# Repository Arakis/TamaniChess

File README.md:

TamaniChess
-----------

TamaniChess is a open source chess computer. This project contains:
* The construction plan of the chess computer
  * the wodden case
  * the electrical circuits
  * needed parts
* The software, written in C#. It controls the chess board, the display and the chess engine
* The "Stockfish" chess engine: http://stockfishchess.org/

Common Questions
----------------

Q. Is TamaniChess Open Source?  
A. TamaniChess's License is a modified version of the standard BSD license. The primary modification is that we do not allow commercial distribution or use of TamaniChess, in order to limit some of the obvious abuses of the code and construction plans. Because of this modification, TamaniChess's license does not fall under the definition of an Open Source (uppercase) license.
Confusingly, TamaniChess is often referred to as open source (lowercase), as its development shares much in common with other open source projects. However, in spite of its freely available source code, TamaniChess may not be used in a commercial setting, as specified by its license.

Q. Can I include TamaniChess with my product?  
A. No. TamaniChess is not licensed for commercial use. Using TamaniChess as a "freebie" or including it at "no cost" with your product still constitutes commerical usage and is forbidden by the license.

Q. Can I sell my product with the TamaniChess logo on it?  
A. No. Putting the logo on your product makes it appear that the product is something officially endorsed by Sebastian Loncar, and constitutes trademark infringement.

Q. Can I use the TamaniChess logo to advertise my product?  
A. No. Using the logo in your advertising makes it appear that the product is something officially endorsed by Sebastian Loncar, and constitutes trademark infringement.

Q. Can I use the term "TamaniChess" in the name of my software?  
A. Generally, no, especially if it is something that is sold. However, if you are producing a free TamaniChess-related piece of software, it is common that permission is granted. Send a query to double- check first, please.

Q. Can I put an arcade cabinet running TamaniChess in a public location?  
A. No. This this a commercial use of TamaniChess and is prohibited by the license. Even if you don't charge money, putting a machine in a public location is "operating" an arcade machine and falls under commercial rules in most locations.

Q. Can my non-profit use TamaniChess or an arcade cabinet running TamaniChess to help raise money?  
A. No, sorry. Even for the most worthwhile cause, this still is a commercial use of TamaniChess and is prohibited by the license.

Q. How do I obtain a license to the TamaniChess source code?  
A. You can't. See the Copyright section above.

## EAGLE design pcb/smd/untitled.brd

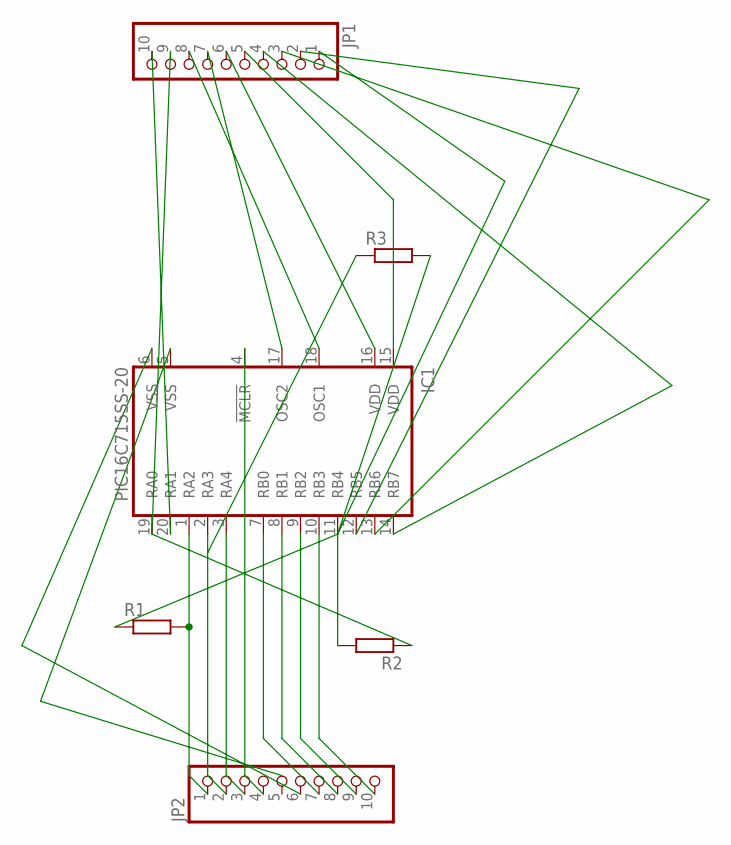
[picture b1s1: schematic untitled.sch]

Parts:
IC1: PIC16C715SS-20; SSOP20
JP1, JP2: PINHD-1X10; 1X10
R1: R-EU_0207/10; 0207/10
R2, R3: R-EU_0204/2V; 0204V

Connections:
unnamed: IC1.1 (RA2), JP2.1, R1.2
unnamed: IC1.2 (RA3), JP2.2, R3.1
unnamed: IC1.3 (RA4), JP2.3
unnamed: IC1.4 (!MCLR), JP2.4
unnamed: IC1.6 (VSS), JP2.6
unnamed: IC1.7 (RB0), JP2.7
unnamed: IC1.8 (RB1), JP2.8
unnamed: IC1.9 (RB2), JP2.9
unnamed: IC1.10 (RB3), JP2.10
unnamed: IC1.11 (RB4), JP1.1, R1.1, R2.2, R3.2
unnamed: IC1.12 (RB5), JP1.2
unnamed: IC1.13 (RB6), JP1.3
unnamed: IC1.14 (RB7), JP1.4
unnamed: IC1.15 (VDD), JP1.5
unnamed: IC1.16 (VDD), JP1.6
unnamed: IC1.17 (OSC2), JP1.7
unnamed: IC1.18 (OSC1), JP1.8
unnamed: IC1.19 (RA0), JP1.9, R2.1
unnamed: IC1.20 (RA1), JP1.10

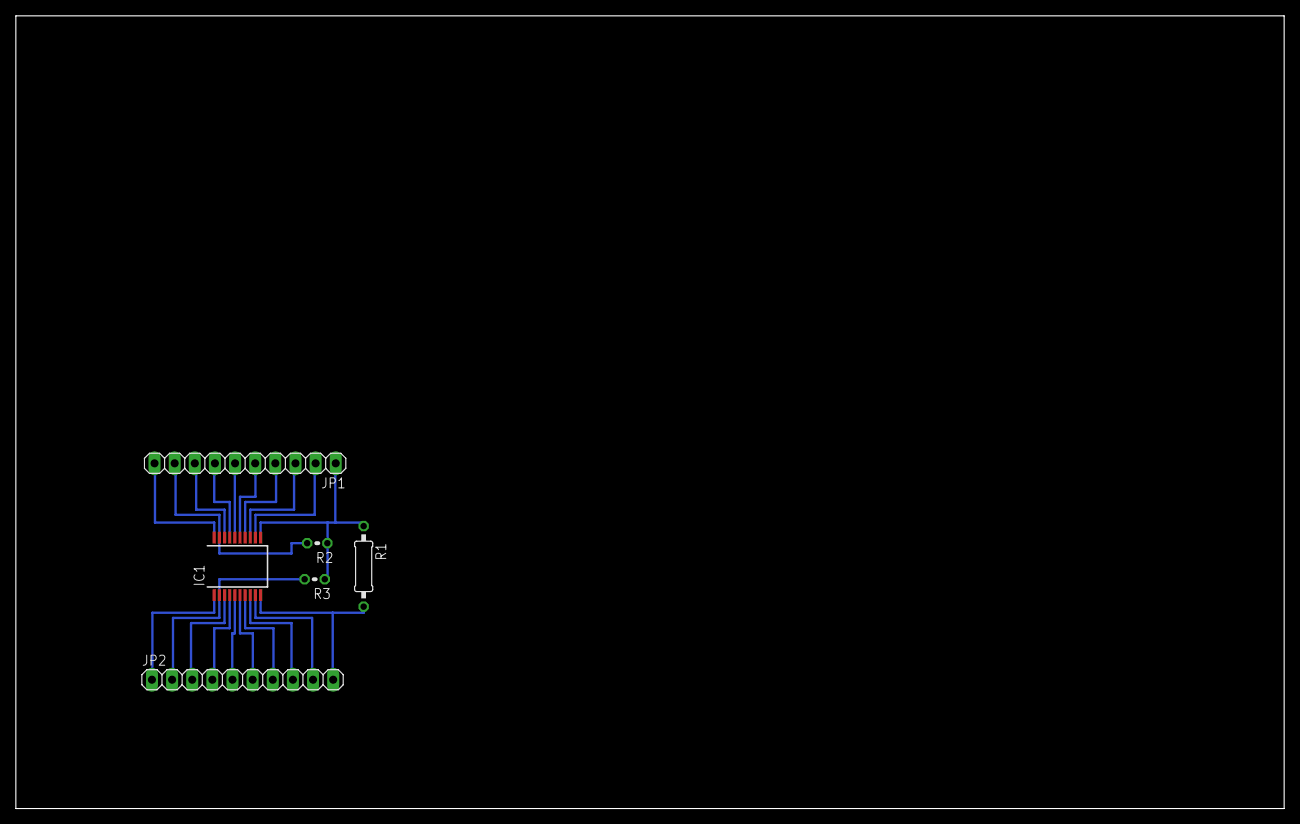
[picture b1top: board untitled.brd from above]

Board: 2 copper layers, 160.0 x 100.0 mm, 6 parts (0 on the bottom side), 19 nets.

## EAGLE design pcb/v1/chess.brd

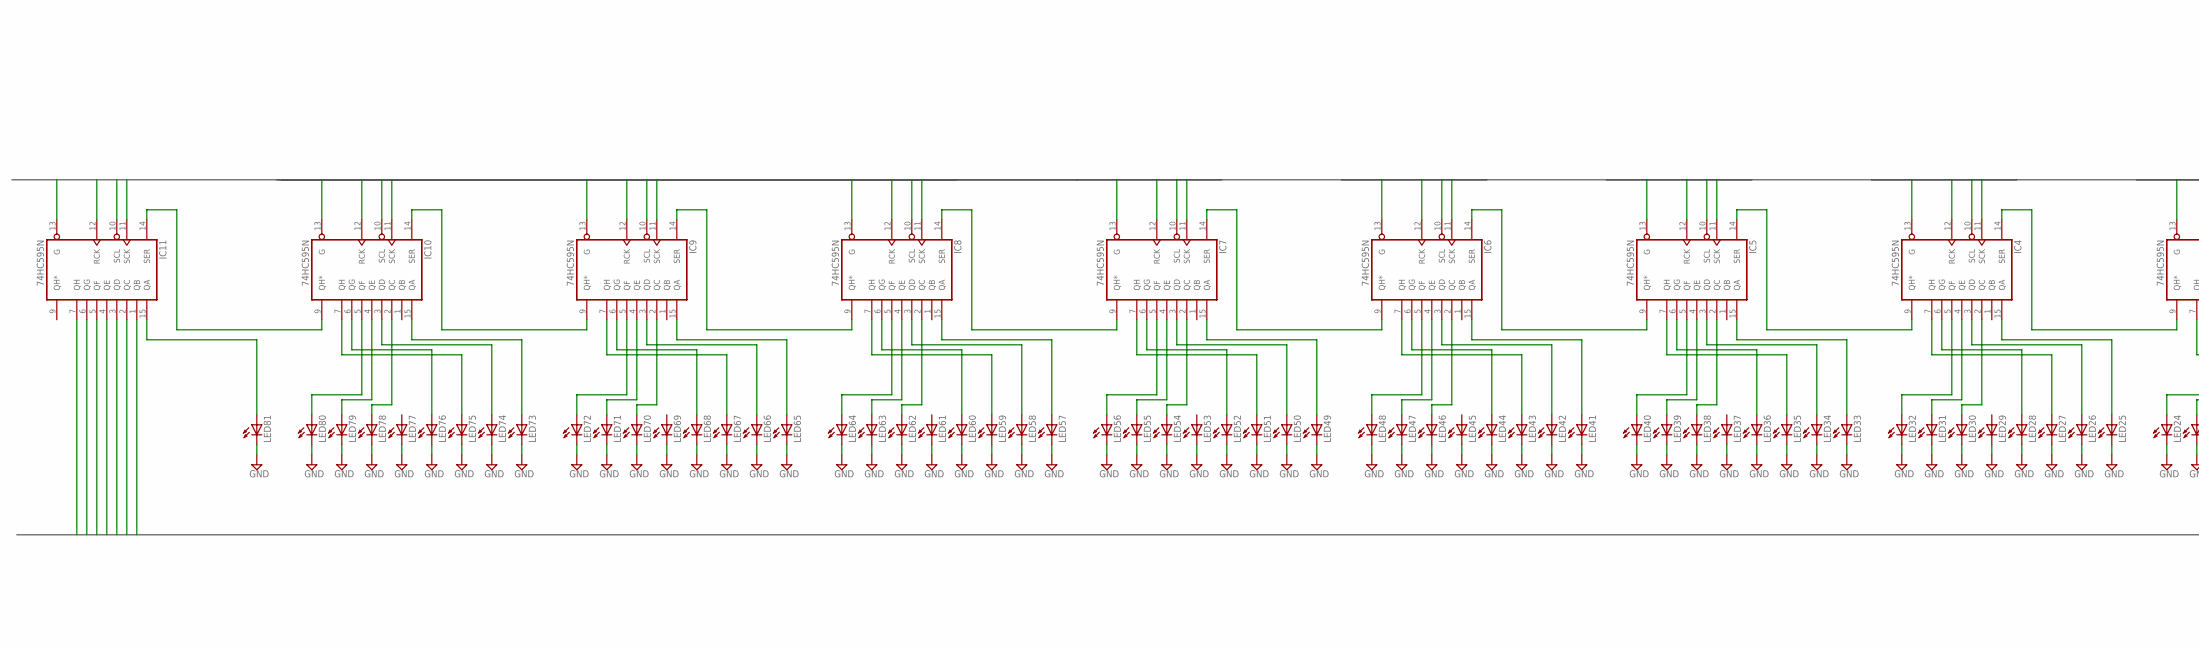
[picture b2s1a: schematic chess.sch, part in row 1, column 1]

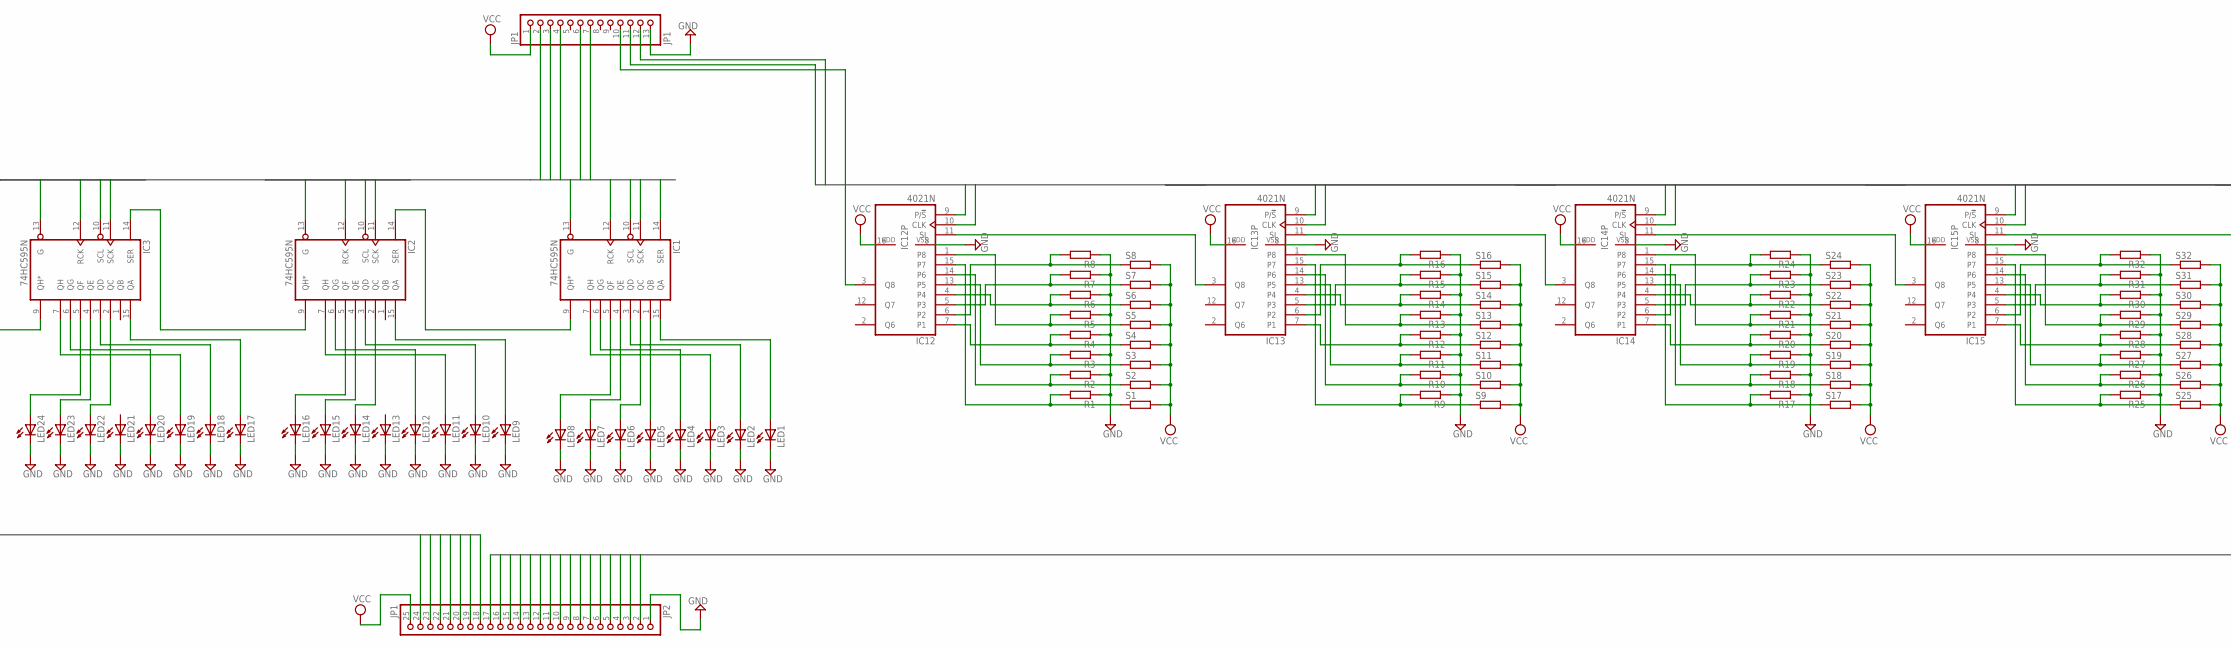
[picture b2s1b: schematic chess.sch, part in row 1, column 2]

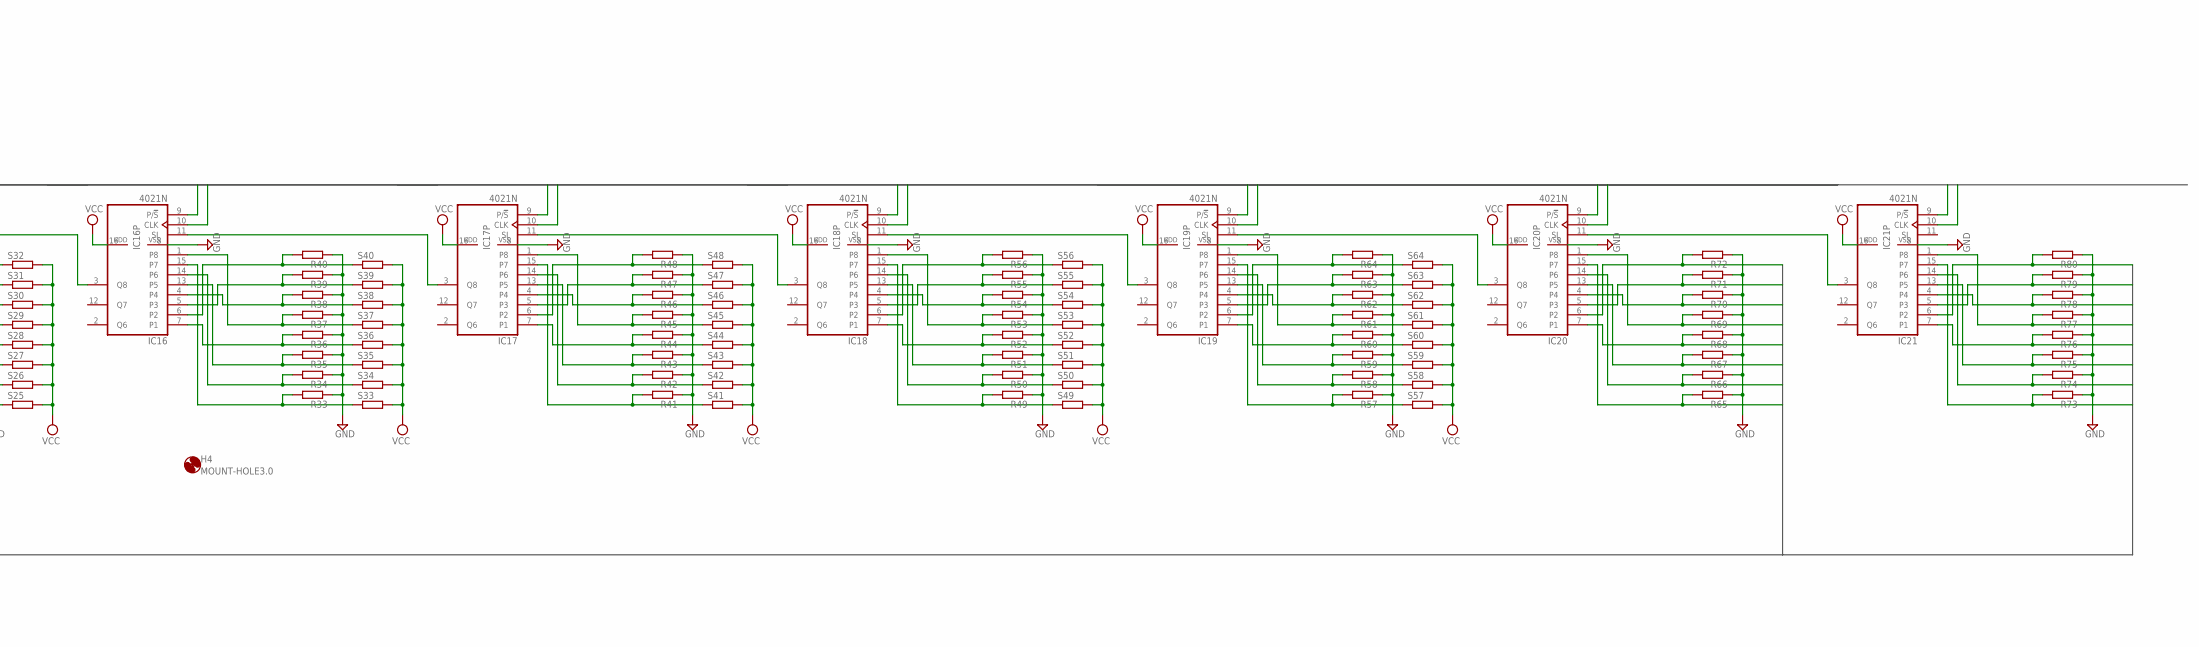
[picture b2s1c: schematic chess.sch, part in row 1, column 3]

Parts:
H4: MOUNT-HOLE3.0; 3,0
IC1, IC2, IC3, IC4, IC5, IC6, IC7, IC8, IC9, IC10, IC11: 74HC595N; DIL16
IC12, IC13, IC14, IC15, IC16, IC17, IC18, IC19, IC20, IC21: 4021N; DIL16
JP1: JP1; 1X13
JP2: JP1; 1X25
LED1, LED2, LED3, LED4, LED5, LED6, LED7, LED8, LED9, LED10, LED11, LED12, LED13, LED14, LED15, LED16, LED17, LED18, LED19, LED20, LED21, LED22, LED23, LED24, LED25, LED26, LED27, LED28, LED29, LED30, LED31, LED32, LED33, LED34, LED35, LED36, LED37, LED38, LED39, LED40, LED41, LED42, LED43, LED44, LED45, LED46, LED47, LED48, LED49, LED50, LED51, LED52, LED53, LED54, LED55, LED56, LED57, LED58, LED59, LED60, LED61, LED62, LED63, LED64, LED65, LED66, LED67, LED68, LED69, LED70, LED71, LED72, LED73, LED74, LED75, LED76, LED77, LED78, LED79, LED80, LED81: LED5MM
R1, R2, R3, R4, R5, R6, R7, R8, R9, R10, R11, R12, R13, R14, R15, R16, R17, R18, R19, R20, R21, R22, R23, R24, R25, R26, R27, R28, R29, R30, R31, R32, R33, R34, R35, R36, R37, R38, R39, R40, R41, R42, R43, R44, R45, R46, R47, R48, R49, R50, R51, R52, R53, R54, R55, R56, R57, R58, R59, R60, R61, R62, R63, R64, R65, R66, R67, R68, R69, R70, R71, R72, R73, R74, R75, R76, R77, R78, R79, R80: R-EU_0207/15; 0207/15
S1, S2, S3, S4, S5, S6, S7, S8, S9, S10, S11, S12, S13, S14, S15, S16, S17, S18, S19, S20, S21, S22, S23, S24, S25, S26, S27, S28, S29, S30, S31, S32, S33, S34, S35, S36, S37, S38, S39, S40, S41, S42, S43, S44, S45, S46, S47, S48, S49, S50, S51, S52, S53, S54, S55, S56, S57, S58, S59, S60, S61, S62, S63, S64: R-EU_0617/22; 0617/22

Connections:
CLK: IC12.10 (CLK), IC13.10 (CLK), IC14.10 (CLK), IC15.10 (CLK), IC16.10 (CLK), IC17.10 (CLK), IC18.10 (CLK), IC19.10 (CLK), IC20.10 (CLK), IC21.10 (CLK), JP1.11
G: IC1.13 (G), IC2.13 (G), IC3.13 (G), IC4.13 (G), IC5.13 (G), IC6.13 (G), IC7.13 (G), IC8.13 (G), IC9.13 (G), IC10.13 (G), IC11.13 (G), JP1.3
GND: IC1.8 (GND), IC2.8 (GND), IC3.8 (GND), IC4.8 (GND), IC5.8 (GND), IC6.8 (GND), IC7.8 (GND), IC8.8 (GND), IC9.8 (GND), IC10.8 (GND), IC11.8 (GND), IC12.8 (VSS), IC13.8 (VSS), IC14.8 (VSS), IC15.8 (VSS), IC16.8 (VSS), IC17.8 (VSS), IC18.8 (VSS), IC19.8 (VSS), IC20.8 (VSS), IC21.8 (VSS), JP1.13, JP2.1, LED1.K (C), LED2.K (C), LED3.K (C), LED4.K (C), LED5.K (C), LED6.K (C), LED7.K (C), LED8.K (C), LED9.K (C), LED10.K (C), LED11.K (C), LED12.K (C), LED13.K (C), LED14.K (C), LED15.K (C), LED16.K (C), LED17.K (C), LED18.K (C), LED19.K (C), LED20.K (C), LED21.K (C), LED22.K (C), LED23.K (C), LED24.K (C), LED25.K (C), LED26.K (C), LED27.K (C), LED28.K (C), LED29.K (C), LED30.K (C), LED31.K (C), LED32.K (C), LED33.K (C), LED34.K (C), LED35.K (C), LED36.K (C), LED37.K (C), LED38.K (C), LED39.K (C), LED40.K (C), LED41.K (C), LED42.K (C), LED43.K (C), LED44.K (C), LED45.K (C), LED46.K (C), LED47.K (C), LED48.K (C), LED49.K (C), LED50.K (C), LED51.K (C), LED52.K (C), LED53.K (C), LED54.K (C), LED55.K (C), LED56.K (C), LED57.K (C), LED58.K (C), LED59.K (C), LED60.K (C), LED61.K (C), LED62.K (C), LED63.K (C), LED64.K (C), LED65.K (C), LED66.K (C), LED67.K (C), LED68.K (C), LED69.K (C), LED70.K (C), LED71.K (C), LED72.K (C), LED73.K (C), LED74.K (C), LED75.K (C), LED76.K (C), LED77.K (C), LED78.K (C), LED79.K (C), LED80.K (C), LED81.K (C), R1.1, R2.1, R3.1, R4.1, R5.1, R6.1, R7.1, R8.1, R9.1, R10.1, R11.1, R12.1, R13.1, R14.1, R15.1, R16.1, R17.1, R18.1, R19.1, R20.1, R21.1, R22.1, R23.1, R24.1, R25.1, R26.1, R27.1, R28.1, R29.1, R30.1, R31.1, R32.1, R33.1, R34.1, R35.1, R36.1, R37.1, R38.1, R39.1, R40.1, R41.1, R42.1, R43.1, R44.1, R45.1, R46.1, R47.1, R48.1, R49.1, R50.1, R51.1, R52.1, R53.1, R54.1, R55.1, R56.1, R57.1, R58.1, R59.1, R60.1, R61.1, R62.1, R63.1, R64.1, R65.1, R66.1, R67.1, R68.1, R69.1, R70.1, R71.1, R72.1, R73.1, R74.1, R75.1, R76.1, R77.1, R78.1, R79.1, R80.1
unnamed: IC1.9 (QH*), IC2.14 (SER)
unnamed: IC2.15 (QA), LED9.A
unnamed: IC1.15 (QA), LED1.A
unnamed: IC1.1 (QB), LED5.A
unnamed: IC1.2 (QC), LED6.A
unnamed: IC1.3 (QD), LED2.A
unnamed: IC1.4 (QE), LED7.A
unnamed: IC1.5 (QF), LED8.A
unnamed: IC1.6 (QG), LED4.A
unnamed: IC1.7 (QH), LED3.A
unnamed: IC2.2 (QC), LED14.A
unnamed: IC2.3 (QD), LED10.A
unnamed: IC2.4 (QE), LED15.A
unnamed: IC2.5 (QF), LED16.A
unnamed: IC2.6 (QG), LED12.A
unnamed: IC2.7 (QH), LED11.A
unnamed: IC3.15 (QA), LED17.A
unnamed: IC3.2 (QC), LED22.A
unnamed: IC3.3 (QD), LED18.A
unnamed: IC3.4 (QE), LED23.A
unnamed: IC3.5 (QF), LED24.A
unnamed: IC3.6 (QG), LED20.A
unnamed: IC3.7 (QH), LED19.A
unnamed: IC4.15 (QA), LED25.A
unnamed: IC4.2 (QC), LED30.A
unnamed: IC4.3 (QD), LED26.A
unnamed: IC4.4 (QE), LED31.A
unnamed: IC2.9 (QH*), IC3.14 (SER)
unnamed: IC4.5 (QF), LED32.A
unnamed: IC4.6 (QG), LED28.A
unnamed: IC4.7 (QH), LED27.A
unnamed: IC5.15 (QA), LED33.A
unnamed: IC5.2 (QC), LED38.A
unnamed: IC5.3 (QD), LED34.A
unnamed: IC5.4 (QE), LED39.A
unnamed: IC5.5 (QF), LED40.A
unnamed: IC5.6 (QG), LED36.A
unnamed: IC3.9 (QH*), IC4.14 (SER)
unnamed: IC5.7 (QH), LED35.A
unnamed: IC6.15 (QA), LED41.A
unnamed: IC6.2 (QC), LED46.A
unnamed: IC6.3 (QD), LED42.A
unnamed: IC6.4 (QE), LED47.A
unnamed: IC6.5 (QF), LED48.A
unnamed: IC6.6 (QG), LED44.A
unnamed: IC6.7 (QH), LED43.A
unnamed: IC7.15 (QA), LED49.A
unnamed: IC4.9 (QH*), IC5.14 (SER)
unnamed: IC7.2 (QC), LED54.A
unnamed: IC7.3 (QD), LED50.A
unnamed: IC7.4 (QE), LED55.A
unnamed: IC7.5 (QF), LED56.A
unnamed: IC7.6 (QG), LED52.A
unnamed: IC7.7 (QH), LED51.A
unnamed: IC8.15 (QA), LED57.A
unnamed: IC8.2 (QC), LED62.A
unnamed: IC8.3 (QD), LED58.A
unnamed: IC5.9 (QH*), IC6.14 (SER)
unnamed: IC8.4 (QE), LED63.A
unnamed: IC8.5 (QF), LED64.A
unnamed: IC8.6 (QG), LED60.A
unnamed: IC8.7 (QH), LED59.A
unnamed: IC9.15 (QA), LED65.A
unnamed: IC9.2 (QC), LED70.A
unnamed: IC9.3 (QD), LED66.A
unnamed: IC9.4 (QE), LED71.A
unnamed: IC9.5 (QF), LED72.A
unnamed: IC6.9 (QH*), IC7.14 (SER)
unnamed: IC9.6 (QG), LED68.A
unnamed: IC9.7 (QH), LED67.A
unnamed: IC10.15 (QA), LED73.A
unnamed: IC10.2 (QC), LED78.A
unnamed: IC10.3 (QD), LED74.A
unnamed: IC10.4 (QE), LED79.A
unnamed: IC10.5 (QF), LED80.A
unnamed: IC10.6 (QG), LED76.A
unnamed: IC10.7 (QH), LED75.A
unnamed: IC7.9 (QH*), IC8.14 (SER)
unnamed: IC12.1 (P8), R5.2, S5.1
unnamed: IC8.9 (QH*), IC9.14 (SER)
unnamed: IC13.6 (P2), R16.2, S16.1
unnamed: IC13.13 (P5), R11.2, S11.1
unnamed: IC13.7 (P1), R12.2, S12.1
unnamed: IC13.4, R14.2, S14.1
unnamed: IC13.5 (P3), R15.2, S15.1
unnamed: IC13.14 (P6), R10.2, S10.1
unnamed: IC13.15 (P7), R9.2, S9.1
unnamed: IC13.1 (P8), R13.2, S13.1
unnamed: IC9.9 (QH*), IC10.14 (SER)
unnamed: IC12.3 (Q8), JP1.10
unnamed: IC12.6 (P2), R8.2, S8.1
unnamed: IC14.6 (P2), R24.2, S24.1
unnamed: IC12.4, R6.2, S6.1
unnamed: IC12.13 (P5), R3.2, S3.1
unnamed: IC12.7 (P1), R4.2, S4.1
unnamed: IC12.5 (P3), R7.2, S7.1
unnamed: IC11.15 (QA), LED81.A
unnamed: IC10.9 (QH*), IC11.14 (SER)
unnamed: IC12.14 (P6), R2.2, S2.1
unnamed: IC12.15 (P7), R1.2, S1.1
unnamed: IC14.13 (P5), R19.2, S19.1
unnamed: IC14.7 (P1), R20.2, S20.1
unnamed: IC14.4, R22.2, S22.1
unnamed: IC14.5 (P3), R23.2, S23.1
unnamed: IC14.14 (P6), R18.2, S18.1
unnamed: IC14.15 (P7), R17.2, S17.1
unnamed: IC14.1 (P8), R21.2, S21.1
unnamed: IC15.6 (P2), R32.2, S32.1
unnamed: IC15.13 (P5), R27.2, S27.1
unnamed: IC15.7 (P1), R28.2, S28.1
unnamed: IC12.11 (SI), IC13.3 (Q8)
unnamed: IC15.4, R30.2, S30.1
unnamed: IC15.5 (P3), R31.2, S31.1
unnamed: IC15.14 (P6), R26.2, S26.1
unnamed: IC15.15 (P7), R25.2, S25.1
unnamed: IC15.1 (P8), R29.2, S29.1
unnamed: IC16.6 (P2), R40.2, S40.1
unnamed: IC16.13 (P5), R35.2, S35.1
unnamed: IC16.7 (P1), R36.2, S36.1
unnamed: IC16.4, R38.2, S38.1
unnamed: IC13.11 (SI), IC14.3 (Q8)
unnamed: IC16.5 (P3), R39.2, S39.1
unnamed: IC16.14 (P6), R34.2, S34.1
unnamed: IC16.15 (P7), R33.2, S33.1
unnamed: IC16.1 (P8), R37.2, S37.1
unnamed: IC17.6 (P2), R48.2, S48.1
unnamed: IC17.13 (P5), R43.2, S43.1
unnamed: IC17.7 (P1), R44.2, S44.1
unnamed: IC17.4, R46.2, S46.1
unnamed: IC17.5 (P3), R47.2, S47.1
unnamed: IC14.11 (SI), IC15.3 (Q8)
unnamed: IC17.14 (P6), R42.2, S42.1
unnamed: IC17.15 (P7), R41.2, S41.1
unnamed: IC17.1 (P8), R45.2, S45.1
unnamed: IC18.6 (P2), R56.2, S56.1
unnamed: IC18.13 (P5), R51.2, S51.1
unnamed: IC18.7 (P1), R52.2, S52.1
unnamed: IC18.4, R54.2, S54.1
unnamed: IC18.5 (P3), R55.2, S55.1
unnamed: IC18.14 (P6), R50.2, S50.1
unnamed: IC15.11 (SI), IC16.3 (Q8)
unnamed: IC18.15 (P7), R49.2, S49.1
unnamed: IC18.1 (P8), R53.2, S53.1
unnamed: IC19.6 (P2), R64.2, S64.1
unnamed: IC19.13 (P5), R59.2, S59.1
unnamed: IC19.7 (P1), R60.2, S60.1
unnamed: IC19.4, R62.2, S62.1
unnamed: IC19.5 (P3), R63.2, S63.1
unnamed: IC19.14 (P6), R58.2, S58.1
unnamed: IC19.15 (P7), R57.2, S57.1
unnamed: IC16.11 (SI), IC17.3 (Q8)
unnamed: IC19.1 (P8), R61.2, S61.1
unnamed: IC19.11 (SI), IC20.3 (Q8)
unnamed: IC20.11 (SI), IC21.3 (Q8)
unnamed: IC17.11 (SI), IC18.3 (Q8)
unnamed: IC18.11 (SI), IC19.3 (Q8)
PS: IC12.9 (P/!S), IC13.9 (P/!S), IC14.9 (P/!S), IC15.9 (P/!S), IC16.9 (P/!S), IC17.9 (P/!S), IC18.9 (P/!S), IC19.9 (P/!S), IC20.9 (P/!S), IC21.9 (P/!S), JP1.12
RCK: IC1.12 (RCK), IC2.12 (RCK), IC3.12 (RCK), IC4.12 (RCK), IC5.12 (RCK), IC6.12 (RCK), IC7.12 (RCK), IC8.12 (RCK), IC9.12 (RCK), IC10.12 (RCK), IC11.12 (RCK), JP1.4
SCK: IC1.11 (SCK), IC2.11 (SCK), IC3.11 (SCK), IC4.11 (SCK), IC5.11 (SCK), IC6.11 (SCK), IC7.11 (SCK), IC8.11 (SCK), IC9.11 (SCK), IC10.11 (SCK), IC11.11 (SCK), JP1.6
SCL: IC1.10 (SCL), IC2.10 (SCL), IC3.10 (SCL), IC4.10 (SCL), IC5.10 (SCL), IC6.10 (SCL), IC7.10 (SCL), IC8.10 (SCL), IC9.10 (SCL), IC10.10 (SCL), IC11.10 (SCL), JP1.7
SER: IC1.14 (SER), JP1.2
SIDELED1: IC11.1 (QB), JP2.18
SIDELED2: IC11.2 (QC), JP2.19
SIDELED3: IC11.3 (QD), JP2.20
SIDELED4: IC11.4 (QE), JP2.21
SIDELED5: IC11.5 (QF), JP2.22
SIDELED6: IC11.6 (QG), JP2.23
SIDELED7: IC11.7 (QH), JP2.24
SIDESWITCH1: IC20.15 (P7), JP2.2, R65.2
SIDESWITCH2: IC20.14 (P6), JP2.3, R66.2
SIDESWITCH3: IC20.13 (P5), JP2.4, R67.2
SIDESWITCH4: IC20.7 (P1), JP2.5, R68.2
SIDESWITCH5: IC20.1 (P8), JP2.6, R69.2
SIDESWITCH6: IC20.4, JP2.7, R70.2
SIDESWITCH7: IC20.5 (P3), JP2.8, R71.2
SIDESWITCH8: IC20.6 (P2), JP2.9, R72.2
SIDESWITCH9: IC21.15 (P7), JP2.10, R73.2
SIDESWITCH10: IC21.14 (P6), JP2.11, R74.2
SIDESWITCH11: IC21.13 (P5), JP2.12, R75.2
SIDESWITCH12: IC21.7 (P1), JP2.13, R76.2
SIDESWITCH13: IC21.1 (P8), JP2.14, R77.2
SIDESWITCH14: IC21.4, JP2.15, R78.2
SIDESWITCH15: IC21.5 (P3), JP2.16, R79.2
SIDESWITCH16: IC21.6 (P2), JP2.17, R80.2
VCC: IC1.16 (VCC), IC2.16 (VCC), IC3.16 (VCC), IC4.16 (VCC), IC5.16 (VCC), IC6.16 (VCC), IC7.16 (VCC), IC8.16 (VCC), IC9.16 (VCC), IC10.16 (VCC), IC11.16 (VCC), IC12.16 (VDD), IC13.16 (VDD), IC14.16 (VDD), IC15.16 (VDD), IC16.16 (VDD), IC17.16 (VDD), IC18.16 (VDD), IC19.16 (VDD), IC20.16 (VDD), IC21.16 (VDD), JP1.1, JP2.25, S1.2, S2.2, S3.2, S4.2, S5.2, S6.2, S7.2, S8.2, S9.2, S10.2, S11.2, S12.2, S13.2, S14.2, S15.2, S16.2, S17.2, S18.2, S19.2, S20.2, S21.2, S22.2, S23.2, S24.2, S25.2, S26.2, S27.2, S28.2, S29.2, S30.2, S31.2, S32.2, S33.2, S34.2, S35.2, S36.2, S37.2, S38.2, S39.2, S40.2, S41.2, S42.2, S43.2, S44.2, S45.2, S46.2, S47.2, S48.2, S49.2, S50.2, S51.2, S52.2, S53.2, S54.2, S55.2, S56.2, S57.2, S58.2, S59.2, S60.2, S61.2, S62.2, S63.2, S64.2

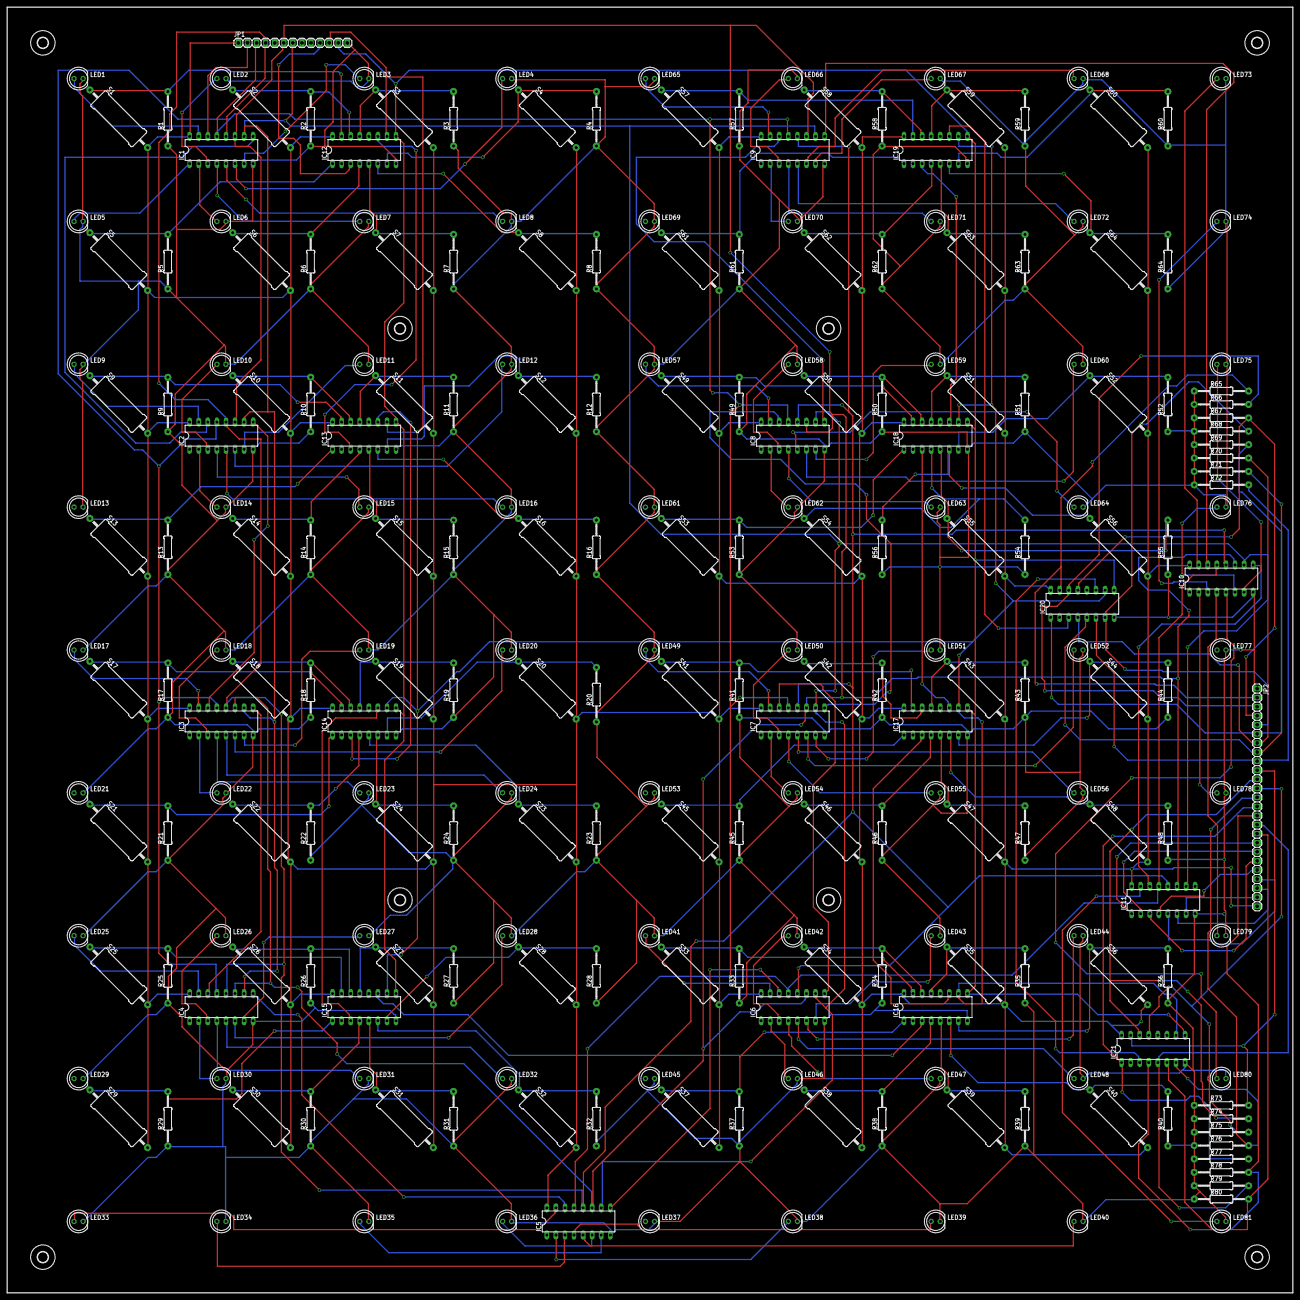
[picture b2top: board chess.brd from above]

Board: 2 copper layers, 360.0 x 360.0 mm, 256 parts (0 on the bottom side), 188 nets.

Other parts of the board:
H1, H2, H3, H5, H6, H7, H8: MOUNT-HOLE3.0; 3,0

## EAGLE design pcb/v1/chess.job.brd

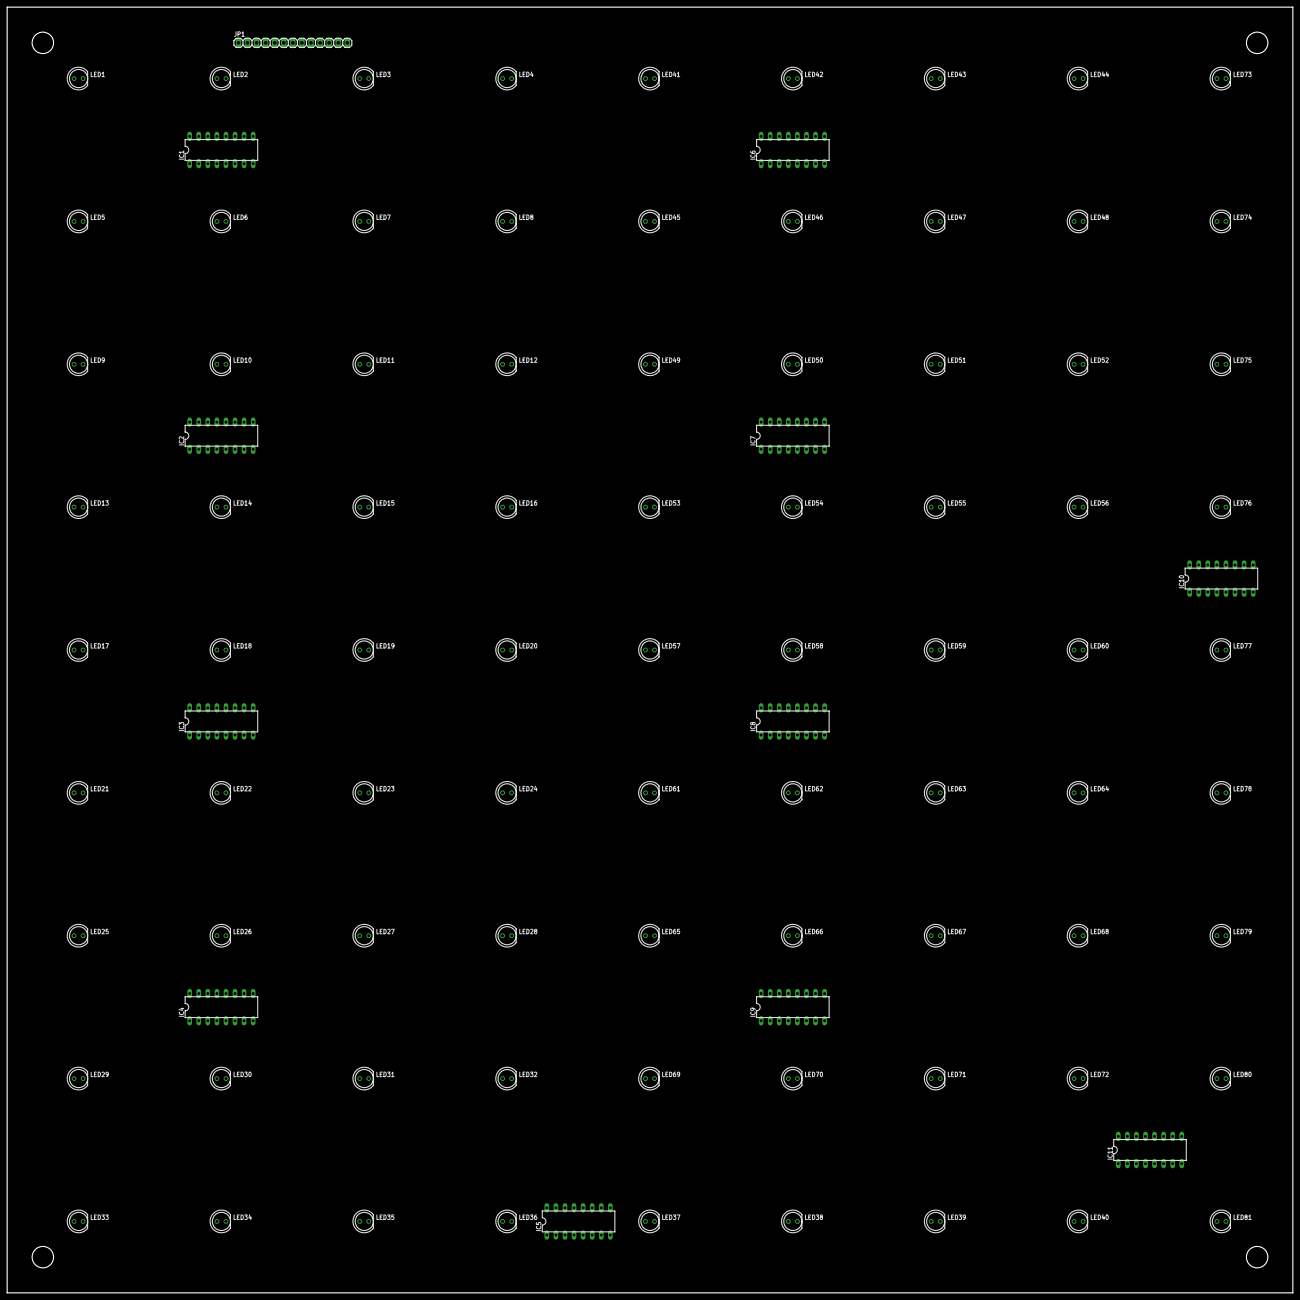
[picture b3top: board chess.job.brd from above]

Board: 2 copper layers, 360.0 x 360.0 mm, 93 parts (0 on the bottom side), 98 nets, no tracks yet.

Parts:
IC1, IC2, IC3, IC4, IC5, IC6, IC7, IC8, IC9, IC10, IC11: 74HC595N; DIL16
JP1: JP1; 1X13
LED1, LED2, LED3, LED4, LED5, LED6, LED7, LED8, LED9, LED10, LED11, LED12, LED13, LED14, LED15, LED16, LED17, LED18, LED19, LED20, LED21, LED22, LED23, LED24, LED25, LED26, LED27, LED28, LED29, LED30, LED31, LED32, LED33, LED34, LED35, LED36, LED37, LED38, LED39, LED40, LED41, LED42, LED43, LED44, LED45, LED46, LED47, LED48, LED49, LED50, LED51, LED52, LED53, LED54, LED55, LED56, LED57, LED58, LED59, LED60, LED61, LED62, LED63, LED64, LED65, LED66, LED67, LED68, LED69, LED70, LED71, LED72, LED73, LED74, LED75, LED76, LED77, LED78, LED79, LED80, LED81: LED5MM

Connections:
G: IC1.13, IC2.13, IC3.13, IC4.13, IC5.13, IC6.13, IC7.13, IC8.13, IC9.13, IC10.13, IC11.13
GND: IC1.8, IC2.8, IC3.8, IC4.8, IC5.8, IC6.8, IC7.8, IC8.8, IC9.8, IC10.8, IC11.8, JP1.13, LED1.K, LED2.K, LED3.K, LED4.K, LED5.K, LED6.K, LED7.K, LED8.K, LED9.K, LED10.K, LED11.K, LED12.K, LED13.K, LED14.K, LED15.K, LED16.K, LED17.K, LED18.K, LED19.K, LED20.K, LED21.K, LED22.K, LED23.K, LED24.K, LED25.K, LED26.K, LED27.K, LED28.K, LED29.K, LED30.K, LED31.K, LED32.K, LED33.K, LED34.K, LED35.K, LED36.K, LED37.K, LED38.K, LED39.K, LED40.K, LED41.K, LED42.K, LED43.K, LED44.K, LED45.K, LED46.K, LED47.K, LED48.K, LED49.K, LED50.K, LED51.K, LED52.K, LED53.K, LED54.K, LED55.K, LED56.K, LED57.K, LED58.K, LED59.K, LED60.K, LED61.K, LED62.K, LED63.K, LED64.K, LED65.K, LED66.K, LED67.K, LED68.K, LED69.K, LED70.K, LED71.K, LED72.K, LED73.K, LED74.K, LED75.K, LED76.K, LED77.K, LED78.K, LED79.K, LED80.K, LED81.K
unnamed: IC1.9, IC2.14
unnamed: IC9.7, LED72.A
unnamed: IC1.7, LED8.A
unnamed: IC1.6, LED7.A
unnamed: IC1.5, LED6.A
unnamed: IC1.4, LED5.A
unnamed: IC1.3, LED4.A
unnamed: IC1.2, LED3.A
unnamed: IC1.1, LED2.A
unnamed: IC1.15, LED1.A
unnamed: IC3.7, LED24.A
unnamed: IC3.6, LED23.A
unnamed: IC2.7, LED16.A
unnamed: IC2.6, LED15.A
unnamed: IC2.5, LED14.A
unnamed: IC2.4, LED13.A
unnamed: IC2.3, LED12.A
unnamed: IC2.2, LED11.A
unnamed: IC2.1, LED10.A
unnamed: IC2.15, LED9.A
unnamed: IC3.5, LED22.A
unnamed: IC3.4, LED21.A
unnamed: IC3.3, LED20.A
unnamed: IC3.2, LED19.A
unnamed: IC3.1, LED18.A
unnamed: IC3.15, LED17.A
unnamed: IC9.6, LED71.A
unnamed: IC2.9, IC3.14
unnamed: IC4.7, LED32.A
unnamed: IC4.6, LED31.A
unnamed: IC4.5, LED30.A
unnamed: IC4.4, LED29.A
unnamed: IC4.3, LED28.A
unnamed: IC4.2, LED27.A
unnamed: IC4.1, LED26.A
unnamed: IC4.15, LED25.A
unnamed: IC9.5, LED70.A
unnamed: IC3.9, IC4.14
unnamed: IC5.7, LED40.A
unnamed: IC5.6, LED39.A
unnamed: IC5.5, LED38.A
unnamed: IC5.4, LED37.A
unnamed: IC5.3, LED36.A
unnamed: IC5.2, LED35.A
unnamed: IC5.1, LED34.A
unnamed: IC5.15, LED33.A
unnamed: IC9.4, LED69.A
unnamed: IC4.9, IC5.14
unnamed: IC6.7, LED48.A
unnamed: IC6.6, LED47.A
unnamed: IC6.5, LED46.A
unnamed: IC6.4, LED45.A
unnamed: IC6.3, LED44.A
unnamed: IC6.2, LED43.A
unnamed: IC6.1, LED42.A
unnamed: IC6.15, LED41.A
unnamed: IC9.3, LED68.A
unnamed: IC5.9, IC6.14
unnamed: IC7.7, LED56.A
unnamed: IC7.6, LED55.A
unnamed: IC7.5, LED54.A
unnamed: IC7.4, LED53.A
unnamed: IC7.3, LED52.A
unnamed: IC7.2, LED51.A
unnamed: IC7.1, LED50.A
unnamed: IC7.15, LED49.A
unnamed: IC9.2, LED67.A
unnamed: IC6.9, IC7.14
unnamed: IC8.7, LED64.A
unnamed: IC8.6, LED63.A
unnamed: IC8.5, LED62.A
unnamed: IC8.4, LED61.A
unnamed: IC8.3, LED60.A
unnamed: IC8.2, LED59.A
unnamed: IC8.1, LED58.A
unnamed: IC8.15, LED57.A
unnamed: IC9.1, LED66.A
unnamed: IC7.9, IC8.14
unnamed: IC9.15, LED65.A
unnamed: IC8.9, IC9.14
unnamed: IC10.7, LED80.A
unnamed: IC10.6, LED79.A
unnamed: IC10.5, LED78.A
unnamed: IC10.4, LED77.A
unnamed: IC10.3, LED76.A
unnamed: IC10.2, LED75.A
unnamed: IC10.1, LED74.A
unnamed: IC10.15, LED73.A
unnamed: IC9.9, IC10.14
unnamed: IC11.15, LED81.A
unnamed: IC10.9, IC11.14
RCK: IC1.12, IC2.12, IC3.12, IC4.12, IC5.12, IC6.12, IC7.12, IC8.12, IC9.12, IC10.12, IC11.12, JP1.4
SCK: IC1.11, IC2.11, IC3.11, IC4.11, IC5.11, IC6.11, IC7.11, IC8.11, IC9.11, IC10.11, IC11.11, JP1.6
SCL: IC1.10, IC2.10, IC3.10, IC4.10, IC5.10, IC6.10, IC7.10, IC8.10, IC9.10, IC10.10, IC11.10, JP1.7
SER: IC1.14, JP1.2, JP1.3
VCC: IC1.16, IC2.16, IC3.16, IC4.16, IC5.16, IC6.16, IC7.16, IC8.16, IC9.16, IC10.16, IC11.16, JP1.1

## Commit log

2013-01-13 updated .gitignore
2013-01-13 Added license
2013-01-13 Added construction plans and pcb layout
2013-01-13 cleanup
2013-01-13 clean up & updating .gitignore
2013-01-13 added bcm2835 driver
2013-01-13 operator overload for TPosition & TMove
2013-01-13 updated computer move handler
2013-01-13 optimized computer move handler
2013-01-14 added pawn conversion
2013-01-15 updated bcm2835 driver to v1.16
2013-01-15 Some refactoring
2013-01-16 Added low level memory operations to speed up the display
2013-01-16 updated bcm2835 driver to 1.17 with own modifications
2013-01-17 Updated ui events
2013-01-17 scrollable ui list
2013-01-21 spi timings
2013-01-21 console input for debug
2013-01-22 vertical orientation
2013-01-24 added screensaver
2013-01-26 improved loading screen. improved sound handling.
2013-01-26 menu
2013-01-28 working on sub menus
2013-02-01 set piece handler
2013-02-02 misc stuff
2013-02-02 improve edit board handlers
2013-02-03 loading and saving games
2013-02-03 added board status text
2013-02-04 split board / game objects
2013-02-05 mainstream setfen / makemove for history logging
2013-02-17 history stuff
2013-02-18 added command line parser
2013-02-18 Using WeakReference for static __exportedPins values
    When not calling dispose, they could never automaticly garbage
    collected, because _exportedPins have always a reference to it. Using
    WeakReference will solve it.
2013-04-09 Changes for new PCB layout
2013-04-09 power up / power down sequence
2013-04-09 changed buttons
2013-04-09 fixed restart in launcher
2013-04-09 repaired loading savegame. moved hardware stuff into new file
2013-04-10 Added undo
2013-04-10 added hint-function
2013-04-10 improved scroll list. remind last scroll position in main menu
2013-04-12 added check and invalid move sound
2013-07-20 updated IO
2013-07-21 added some status texts
2013-07-24 swap color
2013-07-24 swap color, correct figure position, error sound for wrong computer move
2013-08-06 change own color / flip board
2013-08-12 added service option, optimized sound play, avoid restart on exit
2013-08-18 path changes
2013-09-11 text input. Handler priority added.
